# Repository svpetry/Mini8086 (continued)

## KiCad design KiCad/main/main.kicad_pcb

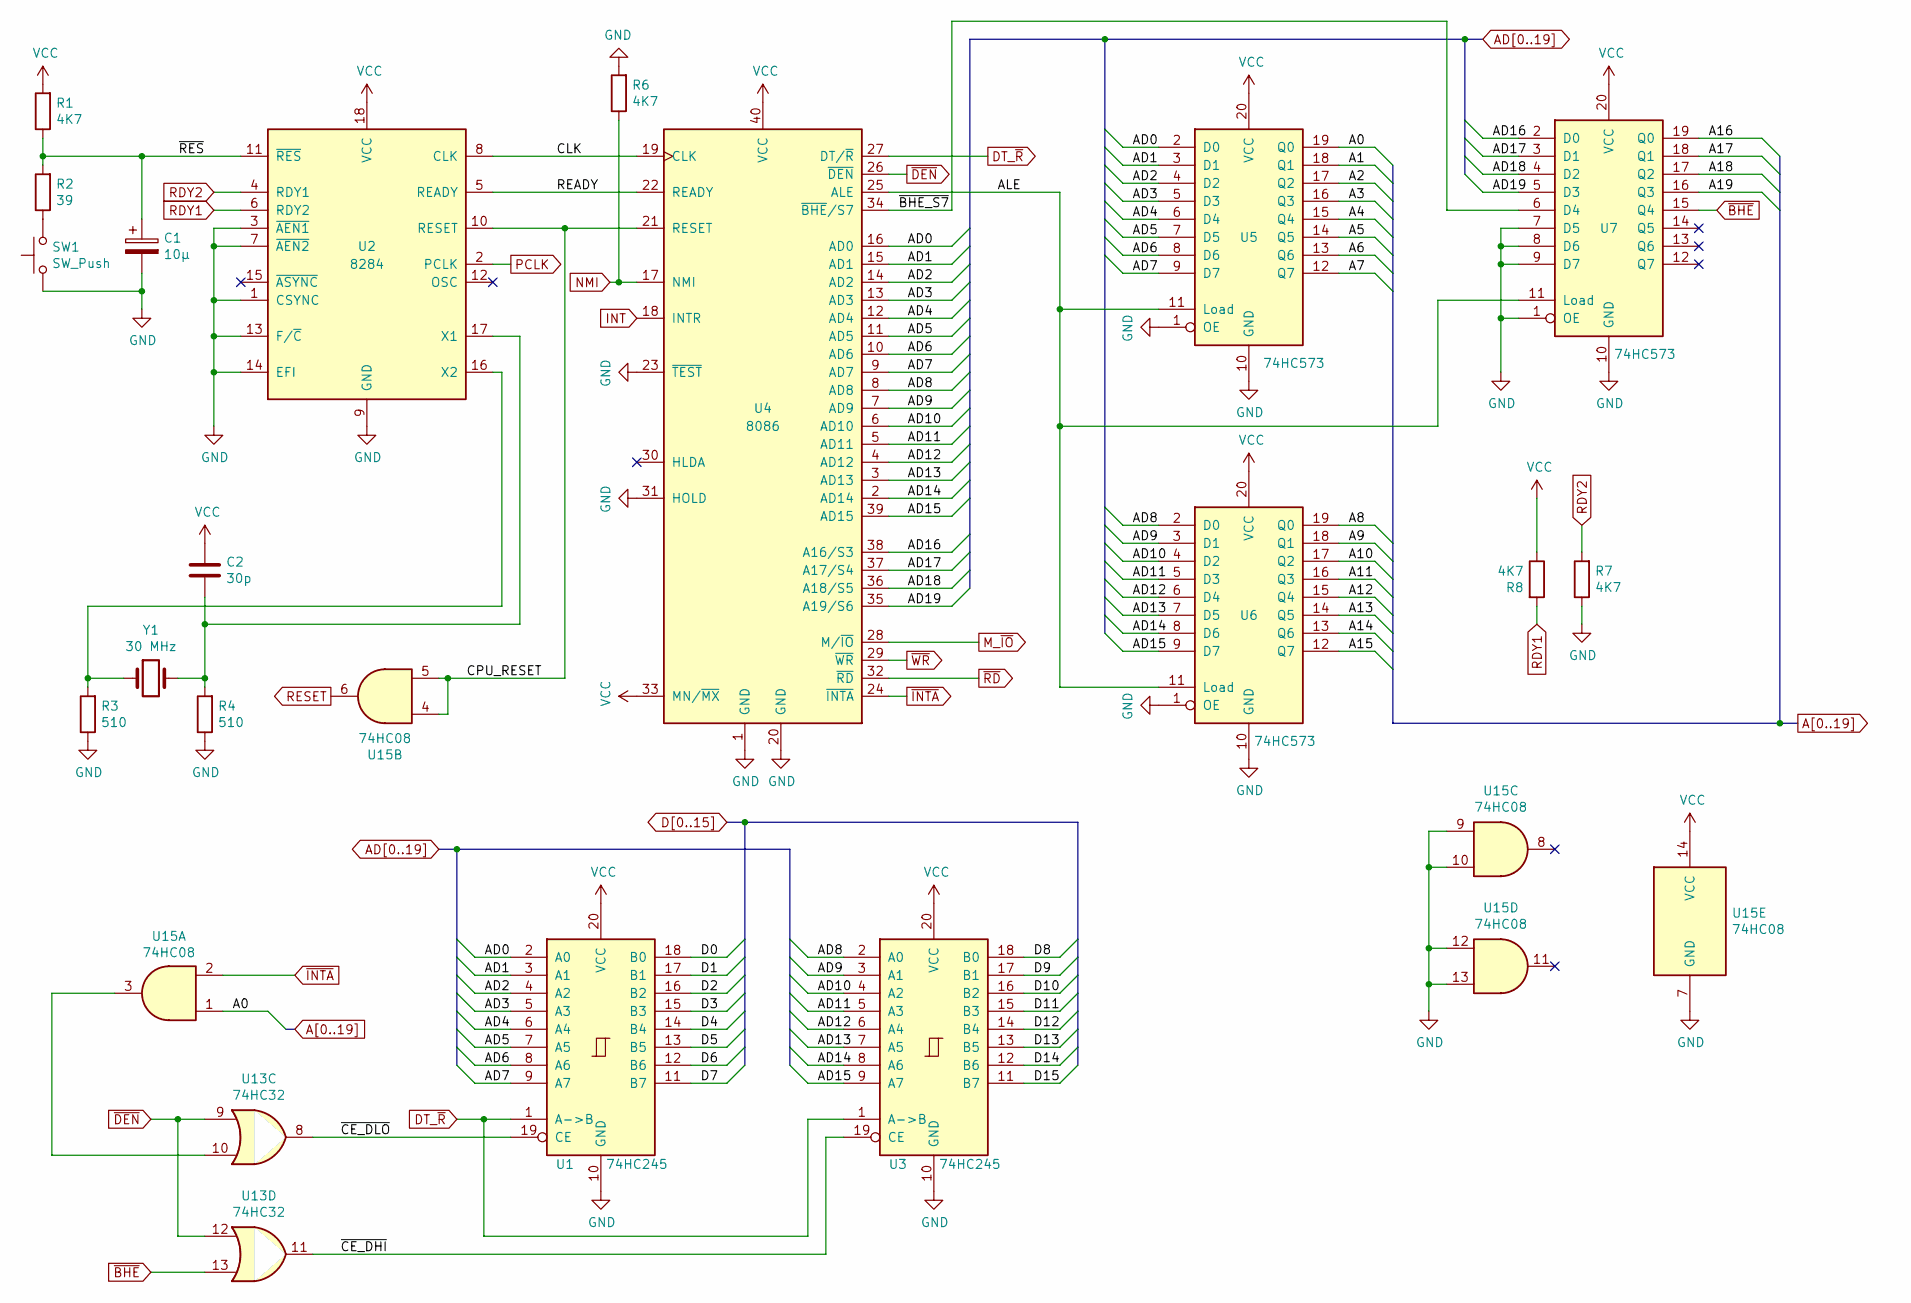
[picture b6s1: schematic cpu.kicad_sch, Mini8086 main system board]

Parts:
C1: 10µ; CP_Radial_D4.0mm_P2.00mm
C2: 30p; C_Disc_D3.0mm_W1.6mm_P2.50mm
R1, R6, R7, R8: 4K7; R_Axial_DIN0207_L6.3mm_D2.5mm_P7.62mm_Horizontal
R2: 39; R_Axial_DIN0207_L6.3mm_D2.5mm_P7.62mm_Horizontal
R3, R4: 510; R_Axial_DIN0207_L6.3mm_D2.5mm_P7.62mm_Horizontal
SW1: SW_Push; SW_PUSH_6mm
U1, U3: 74HC245; DIP-20_W7.62mm_LongPads
U2: 8284; DIP-18_W7.62mm_Socket_LongPads
U4: 8086; DIP-40_W15.24mm_Socket_LongPads
U5, U6, U7: 74HC573; DIP-20_W7.62mm_LongPads
U13: 74HC32; DIP-14_W7.62mm_LongPads
U15: 74HC08; DIP-14_W7.62mm_LongPads
Y1: 30 MHz; Crystal_HC18-U_Vertical

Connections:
/CPU/ALE: U4.25 (ALE), U5.11 (Load), U6.11 (Load), U7.11 (Load)
/CPU/CLK: U2.8 (CLK), U4.19 (CLK)
/CPU/CPU_RESET: U2.10 (RESET), U4.21 (RESET), U15.4, U15.5
/CPU/READY: U2.5 (READY), U4.22 (READY)
/CPU/~CE_DHI: U3.19 (CE), U13.11
/CPU/~CE_DLO: U1.19 (CE), U13.8
/CPU/~RES: C1.1, R1.1, R2.2, U2.11 (~RES)
A0: U5.19 (Q0), U15.1; also elsewhere on the board
A1: U5.18 (Q1); also elsewhere on the board
A2: U5.17 (Q2); also elsewhere on the board
A3: U5.16 (Q3); also elsewhere on the board
A4: U5.15 (Q4); also elsewhere on the board
A5: U5.14 (Q5); also elsewhere on the board
A6: U5.13 (Q6); also elsewhere on the board
A7: U5.12 (Q7); also elsewhere on the board
A8: U6.19 (Q0); also elsewhere on the board
A9: U6.18 (Q1); also elsewhere on the board
A10: U6.17 (Q2); also elsewhere on the board
A11: U6.16 (Q3); also elsewhere on the board
A12: U6.15 (Q4); also elsewhere on the board
A13: U6.14 (Q5); also elsewhere on the board
A14: U6.13 (Q6); also elsewhere on the board
A15: U6.12 (Q7); also elsewhere on the board
A16: U7.19 (Q0); also elsewhere on the board
A17: U7.18 (Q1); also elsewhere on the board
A18: U7.17 (Q2); also elsewhere on the board
A19: U7.16 (Q3); also elsewhere on the board
AD0: U1.2 (A0), U4.16 (AD0), U5.2 (D0)
AD1: U1.3 (A1), U4.15 (AD1), U5.3 (D1)
AD2: U1.4 (A2), U4.14 (AD2), U5.4 (D2)
AD3: U1.5 (A3), U4.13 (AD3), U5.5 (D3)
AD4: U1.6 (A4), U4.12 (AD4), U5.6 (D4)
AD5: U1.7 (A5), U4.11 (AD5), U5.7 (D5)
AD6: U1.8 (A6), U4.10 (AD6), U5.8 (D6)
AD7: U1.9 (A7), U4.9 (AD7), U5.9 (D7)
AD8: U3.2 (A0), U4.8 (AD8), U6.2 (D0)
AD9: U3.3 (A1), U4.7 (AD9), U6.3 (D1)
AD10: U3.4 (A2), U4.6 (AD10), U6.4 (D2)
AD11: U3.5 (A3), U4.5 (AD11), U6.5 (D3)
AD12: U3.6 (A4), U4.4 (AD12), U6.6 (D4)
AD13: U3.7 (A5), U4.3 (AD13), U6.7 (D5)
AD14: U3.8 (A6), U4.2 (AD14), U6.8 (D6)
AD15: U3.9 (A7), U4.39 (AD15), U6.9 (D7)
AD16: U4.38 (A16/S3), U7.2 (D0)
AD17: U4.37 (A17/S4), U7.3 (D1)
AD18: U4.36 (A18/S5), U7.4 (D2)
AD19: U4.35 (A19/S6), U7.5 (D3)
D0: U1.18 (B0); also elsewhere on the board
D1: U1.17 (B1); also elsewhere on the board
D2: U1.16 (B2); also elsewhere on the board
D3: U1.15 (B3); also elsewhere on the board
D4: U1.14 (B4); also elsewhere on the board
D5: U1.13 (B5); also elsewhere on the board
D6: U1.12 (B6); also elsewhere on the board
D7: U1.11 (B7); also elsewhere on the board
D8: U3.18 (B0); also elsewhere on the board
D9: U3.17 (B1); also elsewhere on the board
D10: U3.16 (B2); also elsewhere on the board
D11: U3.15 (B3); also elsewhere on the board
D12: U3.14 (B4); also elsewhere on the board
D13: U3.13 (B5); also elsewhere on the board
D14: U3.12 (B6); also elsewhere on the board
D15: U3.11 (B7); also elsewhere on the board
DT_~R: U1.1 (A->B), U3.1 (A->B), U4.27 (DT/~R)
GND: C1.2, R3.1, R4.1, R6.2, R7.1, SW1.1, U1.10 (GND), U2.1 (CSYNC), U2.3 (~AEN1), U2.7 (~AEN2), U2.9 (GND), U2.13 (F/~C), U2.14 (EFI), U3.10 (GND), U4.1 (GND), U4.20 (GND), U4.23 (~TEST), U4.31 (HOLD), U5.1 (OE), U5.10 (GND), U6.1 (OE), U6.10 (GND), U7.1 (OE), U7.7 (D5), U7.8 (D6), U7.9 (D7), U7.10 (GND), U15.7 (GND), U15.9, U15.10, U15.12, U15.13; also elsewhere on the board
INT: U4.18 (INTR); also elsewhere on the board
M_~IO: U4.28 (M/~IO); also elsewhere on the board
NMI: R6.1, U4.17 (NMI); also elsewhere on the board
unnamed: C2.1, R4.2, U2.17 (X1), Y1.2
unnamed: R2.1, SW1.2
unnamed: R3.2, U2.16 (X2), Y1.1
unnamed: U4.34 (~BHE/S7), U7.6 (D4)
unnamed: U13.10, U15.3
PCLK: U2.2 (PCLK); also elsewhere on the board
RDY1: R8.2, U2.6 (RDY2); also elsewhere on the board
RDY2: R7.2, U2.4 (RDY1); also elsewhere on the board
RESET: U15.6; also elsewhere on the board
VCC: C2.2, R1.2, R8.1, U1.20 (VCC), U2.18 (VCC), U3.20 (VCC), U4.33 (MN/~MX), U4.40 (VCC), U5.20 (VCC), U6.20 (VCC), U7.20 (VCC), U15.14 (VCC); also elsewhere on the board
~BHE: U7.15 (Q4), U13.13; also elsewhere on the board
~DEN: U4.26 (~DEN), U13.9, U13.12
~INTA: U4.24 (~INTA), U15.2; also elsewhere on the board
~RD: U4.32 (~RD); also elsewhere on the board
~WR: U4.29 (~WR); also elsewhere on the board

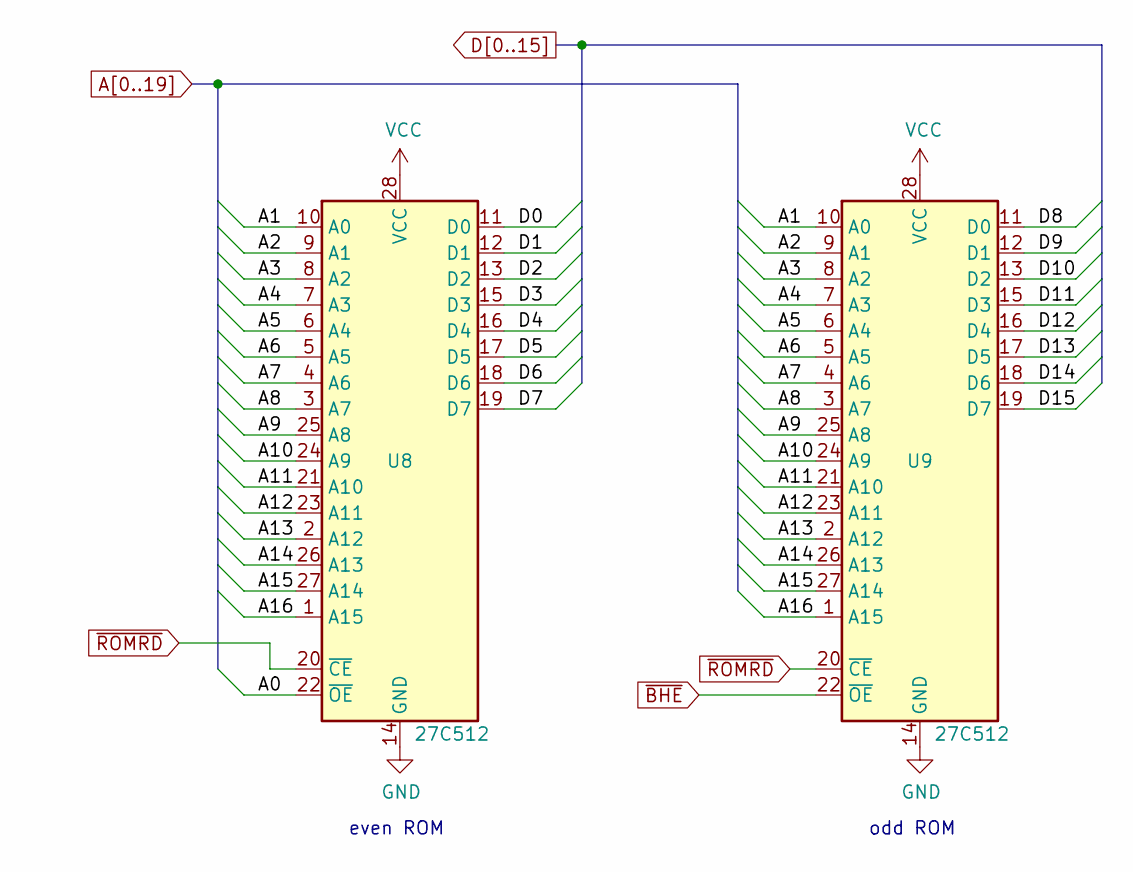
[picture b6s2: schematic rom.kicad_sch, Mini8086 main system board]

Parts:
U8, U9: 27C512; DIP_Socket-28_W11.9_W12.7_W15.24_W17.78_W18.5_3M_228-1277-0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

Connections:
A0: U8.22 (~OE); also elsewhere on the board
A1: U8.10 (A0), U9.10 (A0); also elsewhere on the board
A2: U8.9 (A1), U9.9 (A1); also elsewhere on the board
A3: U8.8 (A2), U9.8 (A2); also elsewhere on the board
A4: U8.7 (A3), U9.7 (A3); also elsewhere on the board
A5: U8.6 (A4), U9.6 (A4); also elsewhere on the board
A6: U8.5 (A5), U9.5 (A5); also elsewhere on the board
A7: U8.4 (A6), U9.4 (A6); also elsewhere on the board
A8: U8.3 (A7), U9.3 (A7); also elsewhere on the board
A9: U8.25 (A8), U9.25 (A8); also elsewhere on the board
A10: U8.24 (A9), U9.24 (A9); also elsewhere on the board
A11: U8.21 (A10), U9.21 (A10); also elsewhere on the board
A12: U8.23 (A11), U9.23 (A11); also elsewhere on the board
A13: U8.2 (A12), U9.2 (A12); also elsewhere on the board
A14: U8.26 (A13), U9.26 (A13); also elsewhere on the board
A15: U8.27 (A14), U9.27 (A14); also elsewhere on the board
A16: U8.1 (A15), U9.1 (A15); also elsewhere on the board
D0: U8.11 (D0); also elsewhere on the board
D1: U8.12 (D1); also elsewhere on the board
D2: U8.13 (D2); also elsewhere on the board
D3: U8.15 (D3); also elsewhere on the board
D4: U8.16 (D4); also elsewhere on the board
D5: U8.17 (D5); also elsewhere on the board
D6: U8.18 (D6); also elsewhere on the board
D7: U8.19 (D7); also elsewhere on the board
D8: U9.11 (D0); also elsewhere on the board
D9: U9.12 (D1); also elsewhere on the board
D10: U9.13 (D2); also elsewhere on the board
D11: U9.15 (D3); also elsewhere on the board
D12: U9.16 (D4); also elsewhere on the board
D13: U9.17 (D5); also elsewhere on the board
D14: U9.18 (D6); also elsewhere on the board
D15: U9.19 (D7); also elsewhere on the board
GND: U8.14 (GND), U9.14 (GND); also elsewhere on the board
VCC: U8.28 (VCC), U9.28 (VCC); also elsewhere on the board
~BHE: U9.22 (~OE); also elsewhere on the board
~ROMRD: U8.20 (~CE), U9.20 (~CE); also elsewhere on the board

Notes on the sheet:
even ROM
odd ROM

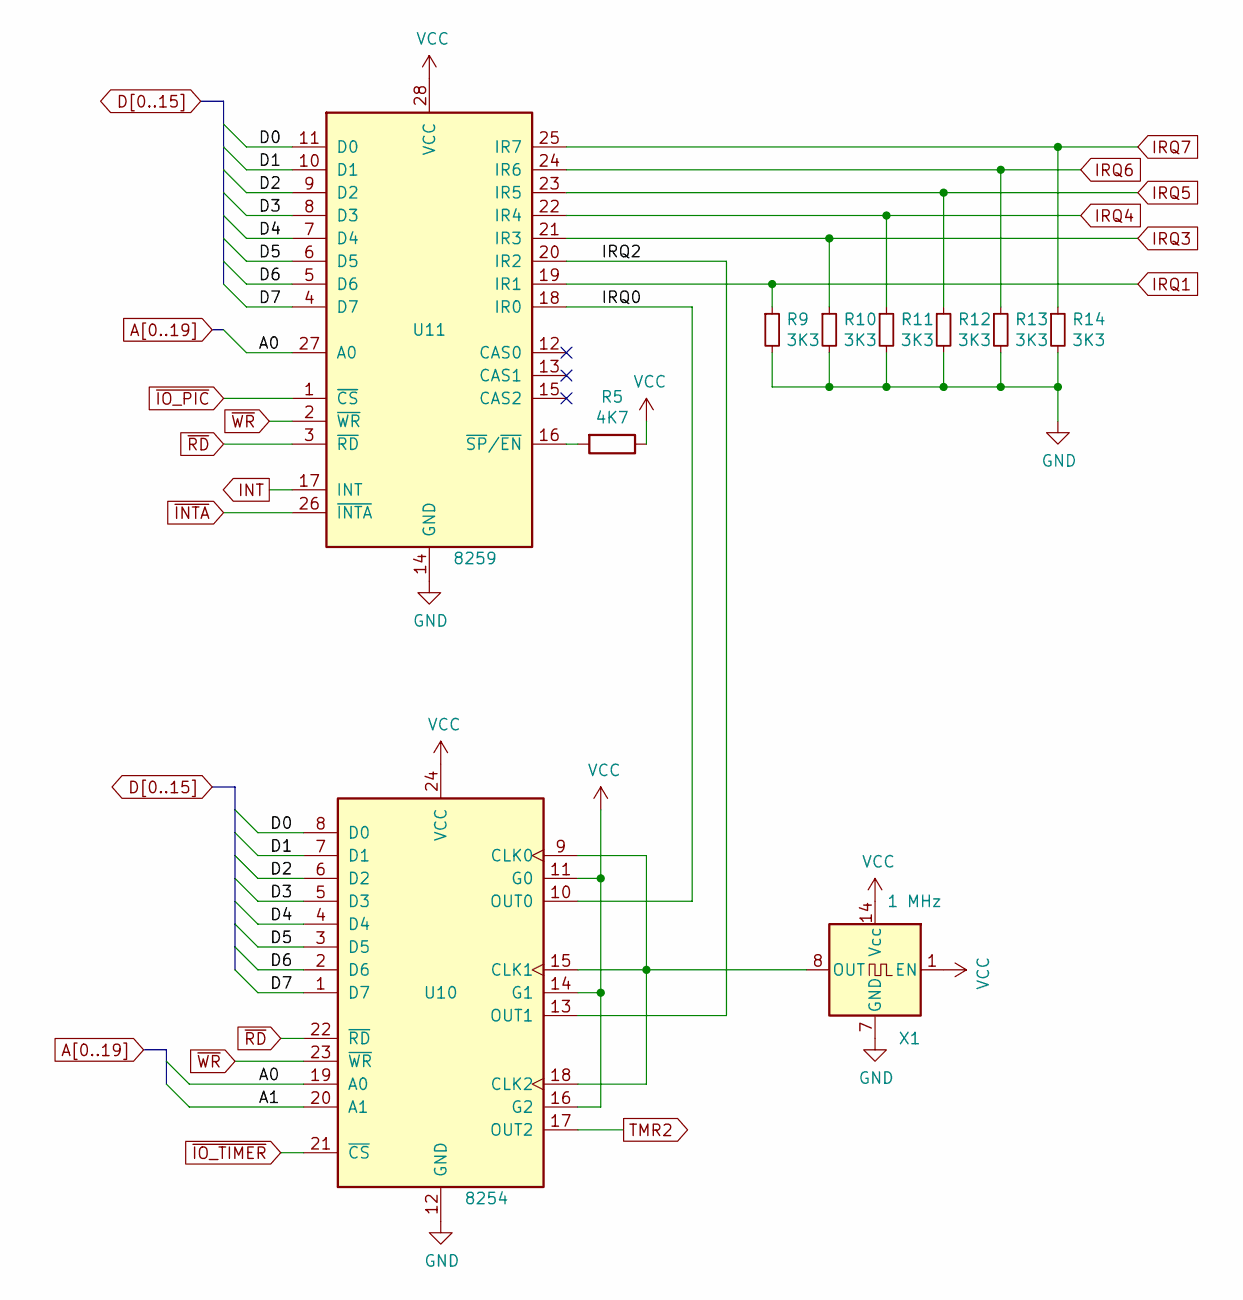
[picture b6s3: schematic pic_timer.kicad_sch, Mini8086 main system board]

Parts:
R5: 4K7; R_Axial_DIN0207_L6.3mm_D2.5mm_P7.62mm_Horizontal
R9, R10, R11, R12, R13, R14: 3K3; R_Axial_DIN0207_L6.3mm_D2.5mm_P2.54mm_Vertical
U10: 8254; DIP-24_W15.24mm_Socket_LongPads
U11: 8259; DIP-28_W15.24mm_Socket_LongPads
X1: 1 MHz; Oscillator_DIP-14

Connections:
/PIC TIMER/IRQ0: U10.10 (OUT0), U11.18 (IR0)
/PIC TIMER/IRQ2: U10.13 (OUT1), U11.20 (IR2)
A0: U10.19 (A0), U11.27 (A0); also elsewhere on the board
A1: U10.20 (A1); also elsewhere on the board
D0: U10.8 (D0), U11.11 (D0); also elsewhere on the board
D1: U10.7 (D1), U11.10 (D1); also elsewhere on the board
D2: U10.6 (D2), U11.9 (D2); also elsewhere on the board
D3: U10.5 (D3), U11.8 (D3); also elsewhere on the board
D4: U10.4 (D4), U11.7 (D4); also elsewhere on the board
D5: U10.3 (D5), U11.6 (D5); also elsewhere on the board
D6: U10.2 (D6), U11.5 (D6); also elsewhere on the board
D7: U10.1 (D7), U11.4 (D7); also elsewhere on the board
GND: R9.2, R10.2, R11.2, R12.2, R13.2, R14.2, U10.12 (GND), U11.14 (GND), X1.7 (GND); also elsewhere on the board
INT: U11.17 (INT); also elsewhere on the board
IRQ1: R9.1, U11.19 (IR1); also elsewhere on the board
IRQ3: R10.1, U11.21 (IR3); also elsewhere on the board
IRQ4: R11.1, U11.22 (IR4); also elsewhere on the board
IRQ5: R12.1, U11.23 (IR5); also elsewhere on the board
IRQ6: R13.1, U11.24 (IR6); also elsewhere on the board
IRQ7: R14.1, U11.25 (IR7); also elsewhere on the board
unnamed: R5.2, U11.16 (~SP/~EN)
unnamed: U10.9 (CLK0), U10.15 (CLK1), U10.18 (CLK2), X1.8 (OUT)
TMR2: U10.17 (OUT2); also elsewhere on the board
VCC: R5.1, U10.11 (G0), U10.14 (G1), U10.16 (G2), U10.24 (VCC), U11.28 (VCC), X1.1 (EN), X1.14 (Vcc); also elsewhere on the board
~INTA: U11.26 (~INTA); also elsewhere on the board
~IO_PIC: U11.1 (~CS); also elsewhere on the board
~IO_TIMER: U10.21 (~CS); also elsewhere on the board
~RD: U10.22 (~RD), U11.3 (~RD); also elsewhere on the board
~WR: U10.23 (~WR), U11.2 (~WR); also elsewhere on the board

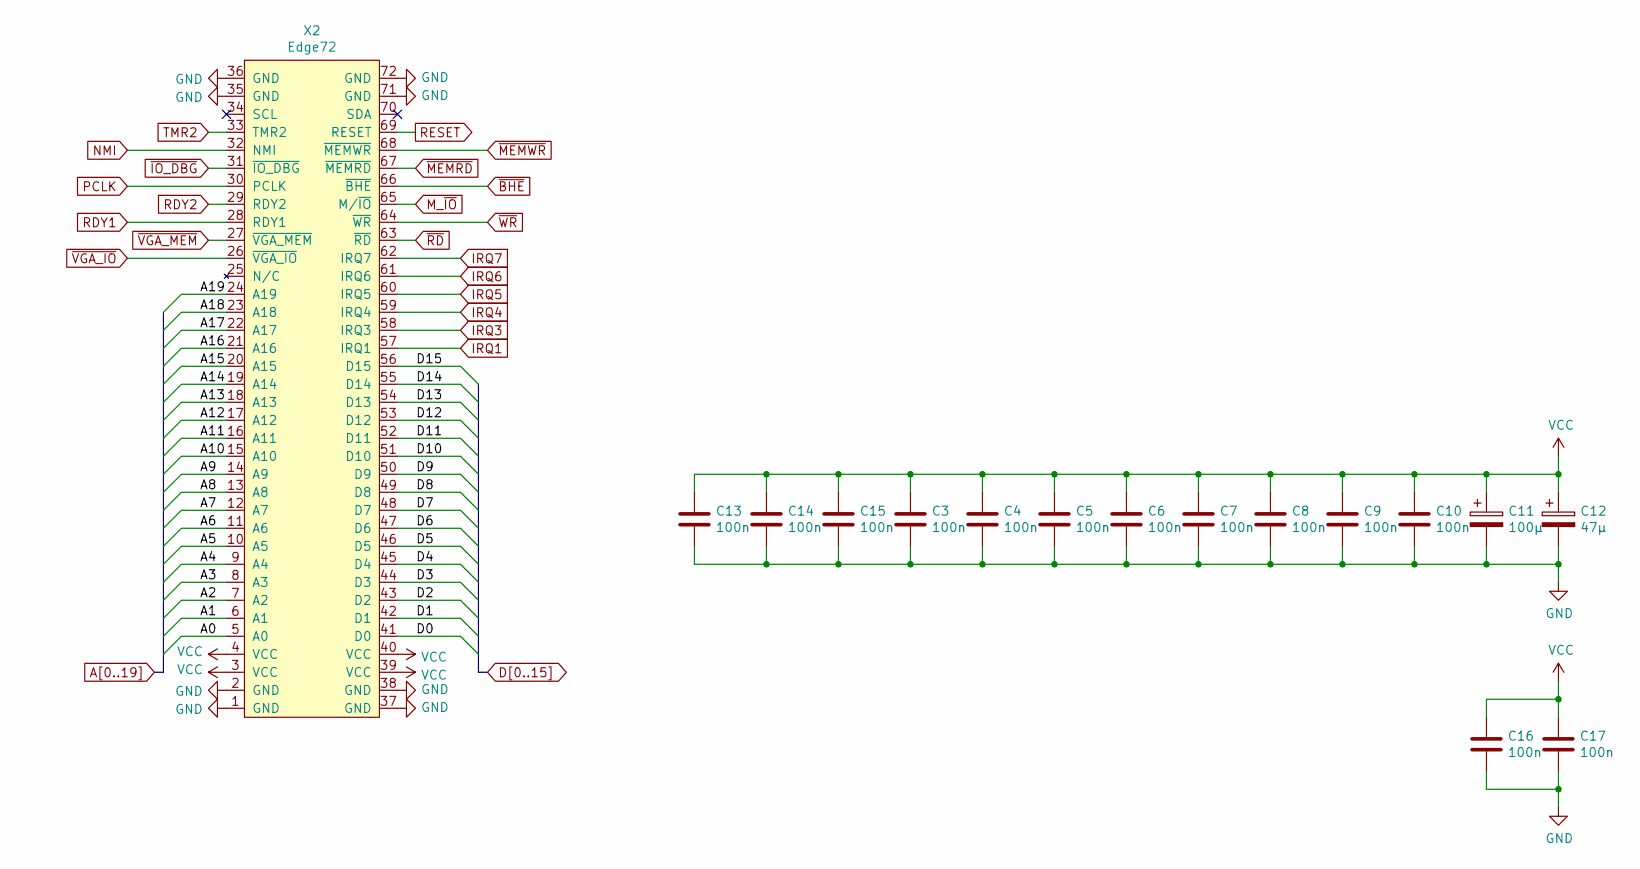
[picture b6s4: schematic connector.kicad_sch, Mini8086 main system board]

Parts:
C3, C4, C5, C6, C7, C8, C9, C10, C13, C14, C15, C16, C17: 100n; C_Disc_D4.3mm_W1.9mm_P5.00mm
C11: 100µ; CP_Radial_D8.0mm_P3.50mm
C12: 47µ; CP_Radial_D4.0mm_P2.00mm
X2: Edge72; BUS_72

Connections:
A0: X2.5 (A0); also elsewhere on the board
A1: X2.6 (A1); also elsewhere on the board
A2: X2.7 (A2); also elsewhere on the board
A3: X2.8 (A3); also elsewhere on the board
A4: X2.9 (A4); also elsewhere on the board
A5: X2.10 (A5); also elsewhere on the board
A6: X2.11 (A6); also elsewhere on the board
A7: X2.12 (A7); also elsewhere on the board
A8: X2.13 (A8); also elsewhere on the board
A9: X2.14 (A9); also elsewhere on the board
A10: X2.15 (A10); also elsewhere on the board
A11: X2.16 (A11); also elsewhere on the board
A12: X2.17 (A12); also elsewhere on the board
A13: X2.18 (A13); also elsewhere on the board
A14: X2.19 (A14); also elsewhere on the board
A15: X2.20 (A15); also elsewhere on the board
A16: X2.21 (A16); also elsewhere on the board
A17: X2.22 (A17); also elsewhere on the board
A18: X2.23 (A18); also elsewhere on the board
A19: X2.24 (A19); also elsewhere on the board
D0: X2.41 (D0); also elsewhere on the board
D1: X2.42 (D1); also elsewhere on the board
D2: X2.43 (D2); also elsewhere on the board
D3: X2.44 (D3); also elsewhere on the board
D4: X2.45 (D4); also elsewhere on the board
D5: X2.46 (D5); also elsewhere on the board
D6: X2.47 (D6); also elsewhere on the board
D7: X2.48 (D7); also elsewhere on the board
D8: X2.49 (D8); also elsewhere on the board
D9: X2.50 (D9); also elsewhere on the board
D10: X2.51 (D10); also elsewhere on the board
D11: X2.52 (D11); also elsewhere on the board
D12: X2.53 (D12); also elsewhere on the board
D13: X2.54 (D13); also elsewhere on the board
D14: X2.55 (D14); also elsewhere on the board
D15: X2.56 (D15); also elsewhere on the board
GND: C3.2, C4.2, C5.2, C6.2, C7.2, C8.2, C9.2, C10.2, C11.2, C12.2, C13.2, C14.2, C15.2, C16.2, C17.2, X2.1 (GND), X2.2 (GND), X2.35 (GND), X2.36 (GND), X2.37 (GND), X2.38 (GND), X2.71 (GND), X2.72 (GND); also elsewhere on the board
IRQ1: X2.57 (IRQ1); also elsewhere on the board
IRQ3: X2.58 (IRQ3); also elsewhere on the board
IRQ4: X2.59 (IRQ4); also elsewhere on the board
IRQ5: X2.60 (IRQ5); also elsewhere on the board
IRQ6: X2.61 (IRQ6); also elsewhere on the board
IRQ7: X2.62 (IRQ7); also elsewhere on the board
M_~IO: X2.65 (M/~IO); also elsewhere on the board
NMI: X2.32 (NMI); also elsewhere on the board
PCLK: X2.30 (PCLK); also elsewhere on the board
RDY1: X2.28 (RDY1); also elsewhere on the board
RDY2: X2.29 (RDY2); also elsewhere on the board
RESET: X2.69 (RESET); also elsewhere on the board
TMR2: X2.33 (TMR2); also elsewhere on the board
VCC: C3.1, C4.1, C5.1, C6.1, C7.1, C8.1, C9.1, C10.1, C11.1, C12.1, C13.1, C14.1, C15.1, C16.1, C17.1, X2.3 (VCC), X2.4 (VCC), X2.39 (VCC), X2.40 (VCC); also elsewhere on the board
~BHE: X2.66 (~BHE); also elsewhere on the board
~IO_DBG: X2.31 (~IO_DBG); also elsewhere on the board
~MEMRD: X2.67 (~MEMRD); also elsewhere on the board
~MEMWR: X2.68 (~MEMWR); also elsewhere on the board
~RD: X2.63 (~RD); also elsewhere on the board
~VGA_IO: X2.26 (~VGA_IO); also elsewhere on the board
~VGA_MEM: X2.27 (~VGA_MEM); also elsewhere on the board
~WR: X2.64 (~WR); also elsewhere on the board

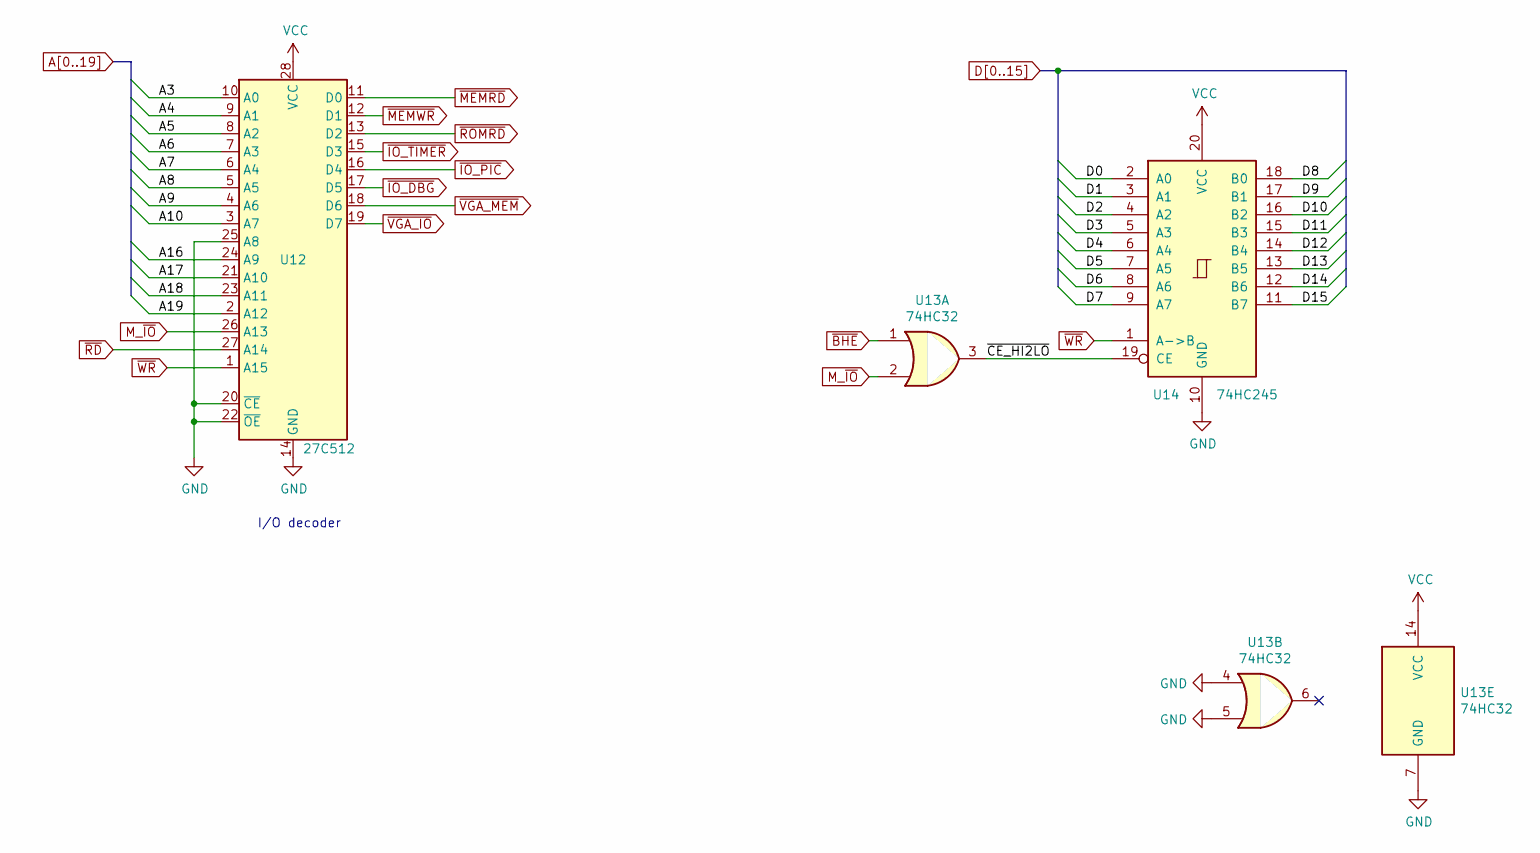
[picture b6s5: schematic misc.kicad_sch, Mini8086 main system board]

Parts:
U12: 27C512; DIP-28_W15.24mm_Socket_LongPads
U13: 74HC32; DIP-14_W7.62mm_LongPads
U14: 74HC245; SO-20_12.8x7.5mm_P1.27mm

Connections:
/glue logic/~CE_HI2LO: U13.3, U14.19 (CE)
A3: U12.10 (A0); also elsewhere on the board
A4: U12.9 (A1); also elsewhere on the board
A5: U12.8 (A2); also elsewhere on the board
A6: U12.7 (A3); also elsewhere on the board
A7: U12.6 (A4); also elsewhere on the board
A8: U12.5 (A5); also elsewhere on the board
A9: U12.4 (A6); also elsewhere on the board
A10: U12.3 (A7); also elsewhere on the board
A16: U12.24 (A9); also elsewhere on the board
A17: U12.21 (A10); also elsewhere on the board
A18: U12.23 (A11); also elsewhere on the board
A19: U12.2 (A12); also elsewhere on the board
D0: U14.2 (A0); also elsewhere on the board
D1: U14.3 (A1); also elsewhere on the board
D2: U14.4 (A2); also elsewhere on the board
D3: U14.5 (A3); also elsewhere on the board
D4: U14.6 (A4); also elsewhere on the board
D5: U14.7 (A5); also elsewhere on the board
D6: U14.8 (A6); also elsewhere on the board
D7: U14.9 (A7); also elsewhere on the board
D8: U14.18 (B0); also elsewhere on the board
D9: U14.17 (B1); also elsewhere on the board
D10: U14.16 (B2); also elsewhere on the board
D11: U14.15 (B3); also elsewhere on the board
D12: U14.14 (B4); also elsewhere on the board
D13: U14.13 (B5); also elsewhere on the board
D14: U14.12 (B6); also elsewhere on the board
D15: U14.11 (B7); also elsewhere on the board
GND: U12.14 (GND), U12.20 (~CE), U12.22 (~OE), U12.25 (A8), U13.4, U13.5, U13.7 (GND), U14.10 (GND); also elsewhere on the board
M_~IO: U12.26 (A13), U13.2; also elsewhere on the board
VCC: U12.28 (VCC), U13.14 (VCC), U14.20 (VCC); also elsewhere on the board
~BHE: U13.1; also elsewhere on the board
~IO_DBG: U12.17 (D5); also elsewhere on the board
~IO_PIC: U12.16 (D4); also elsewhere on the board
~IO_TIMER: U12.15 (D3); also elsewhere on the board
~MEMRD: U12.11 (D0); also elsewhere on the board
~MEMWR: U12.12 (D1); also elsewhere on the board
~RD: U12.27 (A14); also elsewhere on the board
~ROMRD: U12.13 (D2); also elsewhere on the board
~VGA_IO: U12.19 (D7); also elsewhere on the board
~VGA_MEM: U12.18 (D6); also elsewhere on the board
~WR: U12.1 (A15), U14.1 (A->B); also elsewhere on the board

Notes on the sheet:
I/O decoder

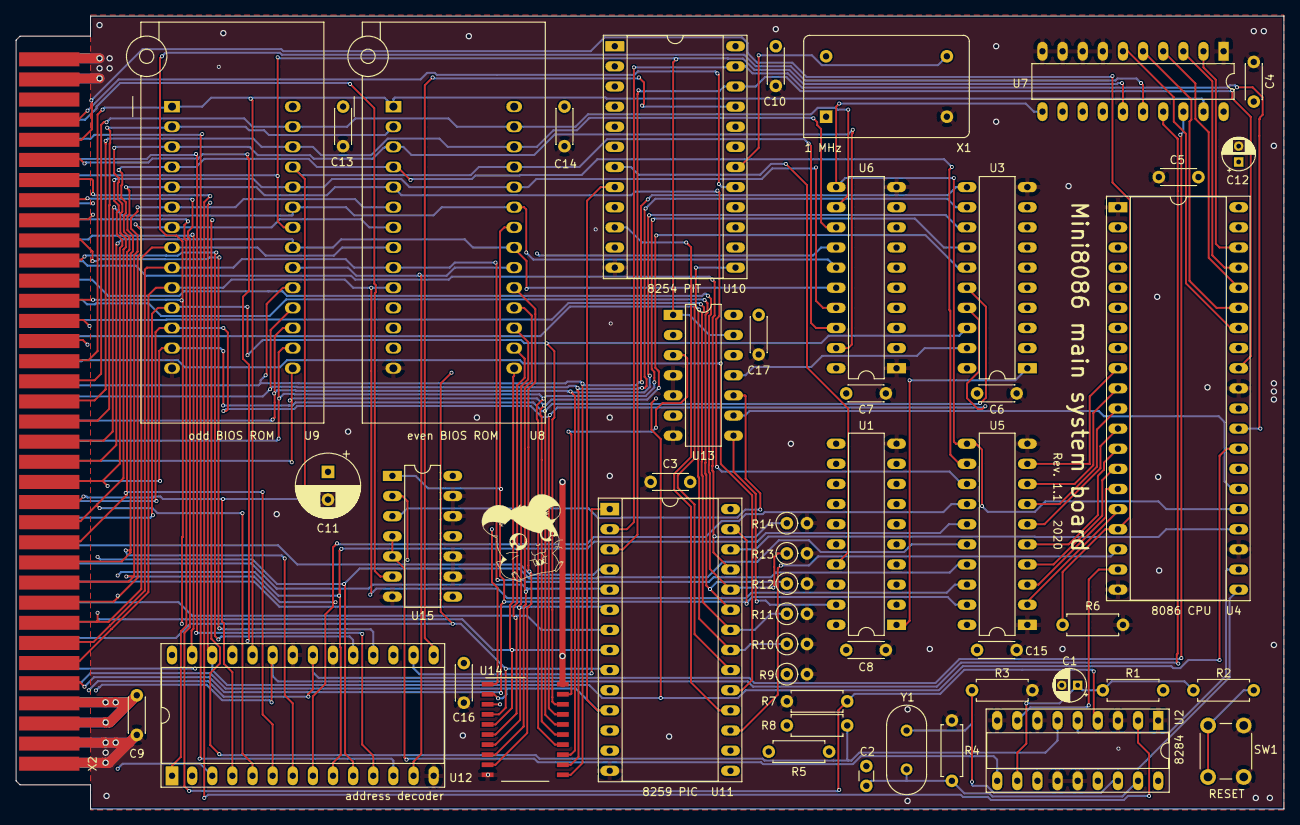
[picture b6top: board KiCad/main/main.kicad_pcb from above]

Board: 4 copper layers, 160.0 x 100.1 mm, 50 parts (0 on the bottom side), 103 nets.

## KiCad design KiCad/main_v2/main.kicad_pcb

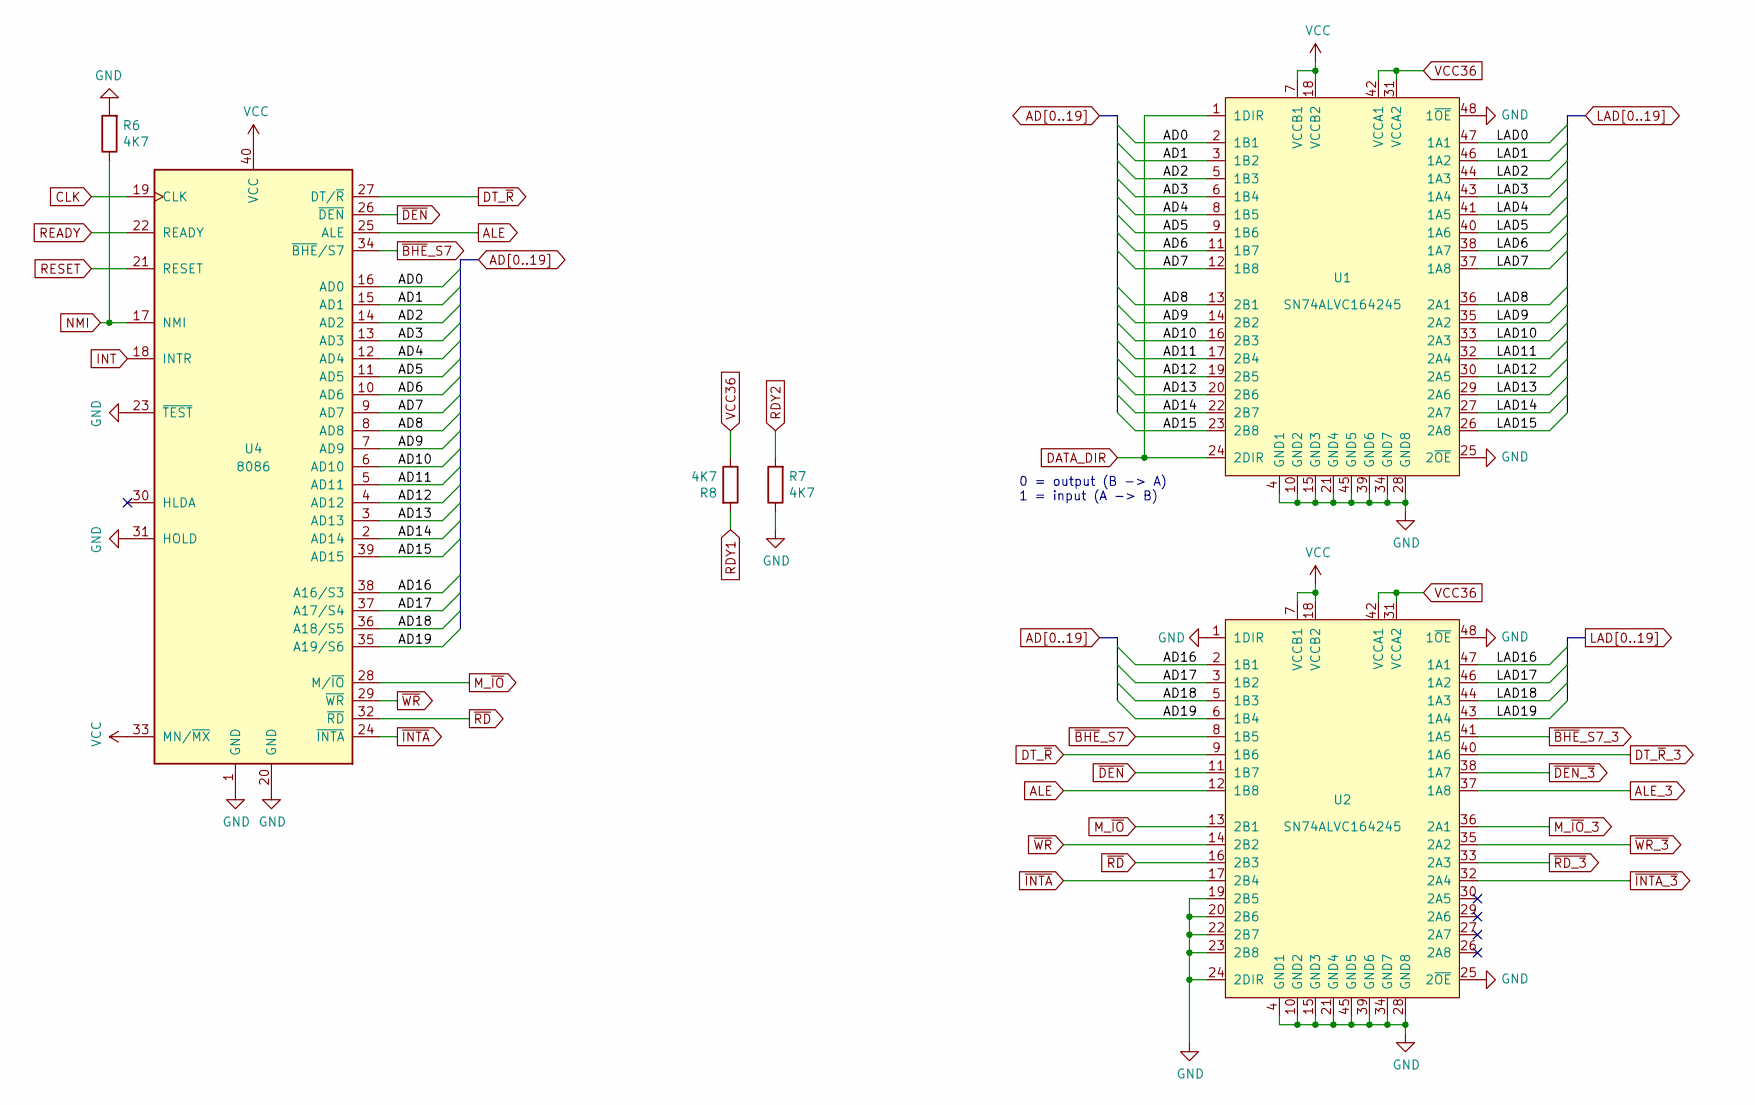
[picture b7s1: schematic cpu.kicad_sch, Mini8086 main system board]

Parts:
R6, R7, R8: 4K7; R_1206_3216Metric
U1, U2: SN74ALVC164245; SSOP-48_7.5x15.9mm_P0.635mm
U4: 8086; DIP-40_W15.24mm_Socket_LongPads

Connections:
AD0: U1.2 (1B1), U4.16 (AD0)
AD1: U1.3 (1B2), U4.15 (AD1)
AD2: U1.5 (1B3), U4.14 (AD2)
AD3: U1.6 (1B4), U4.13 (AD3)
AD4: U1.8 (1B5), U4.12 (AD4)
AD5: U1.9 (1B6), U4.11 (AD5)
AD6: U1.11 (1B7), U4.10 (AD6)
AD7: U1.12 (1B8), U4.9 (AD7)
AD8: U1.13 (2B1), U4.8 (AD8)
AD9: U1.14 (2B2), U4.7 (AD9)
AD10: U1.16 (2B3), U4.6 (AD10)
AD11: U1.17 (2B4), U4.5 (AD11)
AD12: U1.19 (2B5), U4.4 (AD12)
AD13: U1.20 (2B6), U4.3 (AD13)
AD14: U1.22 (2B7), U4.2 (AD14)
AD15: U1.23 (2B8), U4.39 (AD15)
AD16: U2.2 (1B1), U4.38 (A16/S3)
AD17: U2.3 (1B2), U4.37 (A17/S4)
AD18: U2.5 (1B3), U4.36 (A18/S5)
AD19: U2.6 (1B4), U4.35 (A19/S6)
ALE: U2.12 (1B8), U4.25 (ALE)
ALE_3: U2.37 (1A8); also elsewhere on the board
CLK: U4.19 (CLK); also elsewhere on the board
DATA_DIR: U1.1 (1DIR), U1.24 (2DIR); also elsewhere on the board
DT_~R: U2.9 (1B6), U4.27 (DT/~R)
DT_~R~_3: U2.40 (1A6); also elsewhere on the board
GND: R6.2, R7.1, U1.4 (GND1), U1.10 (GND2), U1.15 (GND3), U1.21 (GND4), U1.25 (2~OE), U1.28 (GND8), U1.34 (GND7), U1.39 (GND6), U1.45 (GND5), U1.48 (1~OE), U2.1 (1DIR), U2.4 (GND1), U2.10 (GND2), U2.15 (GND3), U2.19 (2B5), U2.20 (2B6), U2.21 (GND4), U2.22 (2B7), U2.23 (2B8), U2.24 (2DIR), U2.25 (2~OE), U2.28 (GND8), U2.34 (GND7), U2.39 (GND6), U2.45 (GND5), U2.48 (1~OE), U4.1 (GND), U4.20 (GND), U4.23 (~TEST), U4.31 (HOLD); also elsewhere on the board
INT: U4.18 (INTR); also elsewhere on the board
LAD0: U1.47 (1A1); also elsewhere on the board
LAD1: U1.46 (1A2); also elsewhere on the board
LAD2: U1.44 (1A3); also elsewhere on the board
LAD3: U1.43 (1A4); also elsewhere on the board
LAD4: U1.41 (1A5); also elsewhere on the board
LAD5: U1.40 (1A6); also elsewhere on the board
LAD6: U1.38 (1A7); also elsewhere on the board
LAD7: U1.37 (1A8); also elsewhere on the board
LAD8: U1.36 (2A1); also elsewhere on the board
LAD9: U1.35 (2A2); also elsewhere on the board
LAD10: U1.33 (2A3); also elsewhere on the board
LAD11: U1.32 (2A4); also elsewhere on the board
LAD12: U1.30 (2A5); also elsewhere on the board
LAD13: U1.29 (2A6); also elsewhere on the board
LAD14: U1.27 (2A7); also elsewhere on the board
LAD15: U1.26 (2A8); also elsewhere on the board
LAD16: U2.47 (1A1); also elsewhere on the board
LAD17: U2.46 (1A2); also elsewhere on the board
LAD18: U2.44 (1A3); also elsewhere on the board
LAD19: U2.43 (1A4); also elsewhere on the board
M_~IO: U2.13 (2B1), U4.28 (M/~IO); also elsewhere on the board
M_~IO~_3: U2.36 (2A1); also elsewhere on the board
NMI: R6.1, U4.17 (NMI); also elsewhere on the board
RDY1: R8.2; also elsewhere on the board
RDY2: R7.2; also elsewhere on the board
READY: U4.22 (READY); also elsewhere on the board
RESET: U4.21 (RESET); also elsewhere on the board
VCC: U1.7 (VCCB1), U1.18 (VCCB2), U2.7 (VCCB1), U2.18 (VCCB2), U4.33 (MN/~MX), U4.40 (VCC); also elsewhere on the board
VCC36: R8.1, U1.31 (VCCA2), U1.42 (VCCA1), U2.31 (VCCA2), U2.42 (VCCA1); also elsewhere on the board
~BHE~_S7: U2.8 (1B5), U4.34 (~BHE/S7)
~BHE~_S7_3: U2.41 (1A5); also elsewhere on the board
~DEN: U2.11 (1B7), U4.26 (~DEN)
~DEN_3: U2.38 (1A7); also elsewhere on the board
~INTA: U2.17 (2B4), U4.24 (~INTA); also elsewhere on the board
~INTA_3: U2.32 (2A4); also elsewhere on the board
~RD: U2.16 (2B3), U4.32 (~RD); also elsewhere on the board
~RD_3: U2.33 (2A3); also elsewhere on the board
~WR: U2.14 (2B2), U4.29 (~WR); also elsewhere on the board
~WR_3: U2.35 (2A2); also elsewhere on the board

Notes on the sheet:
0 = output (B -> A) 1 = input (A -> B)
